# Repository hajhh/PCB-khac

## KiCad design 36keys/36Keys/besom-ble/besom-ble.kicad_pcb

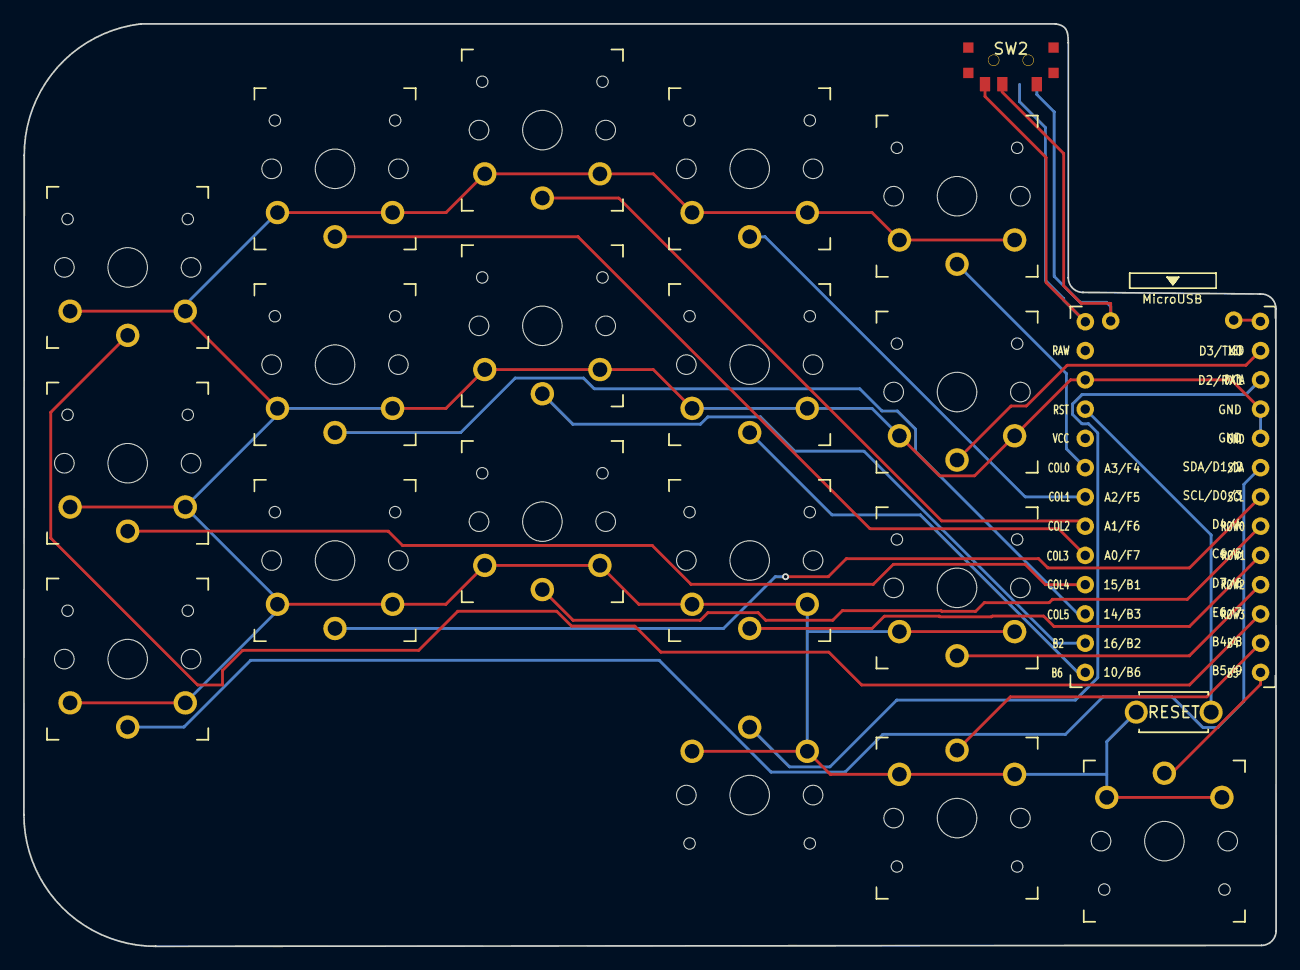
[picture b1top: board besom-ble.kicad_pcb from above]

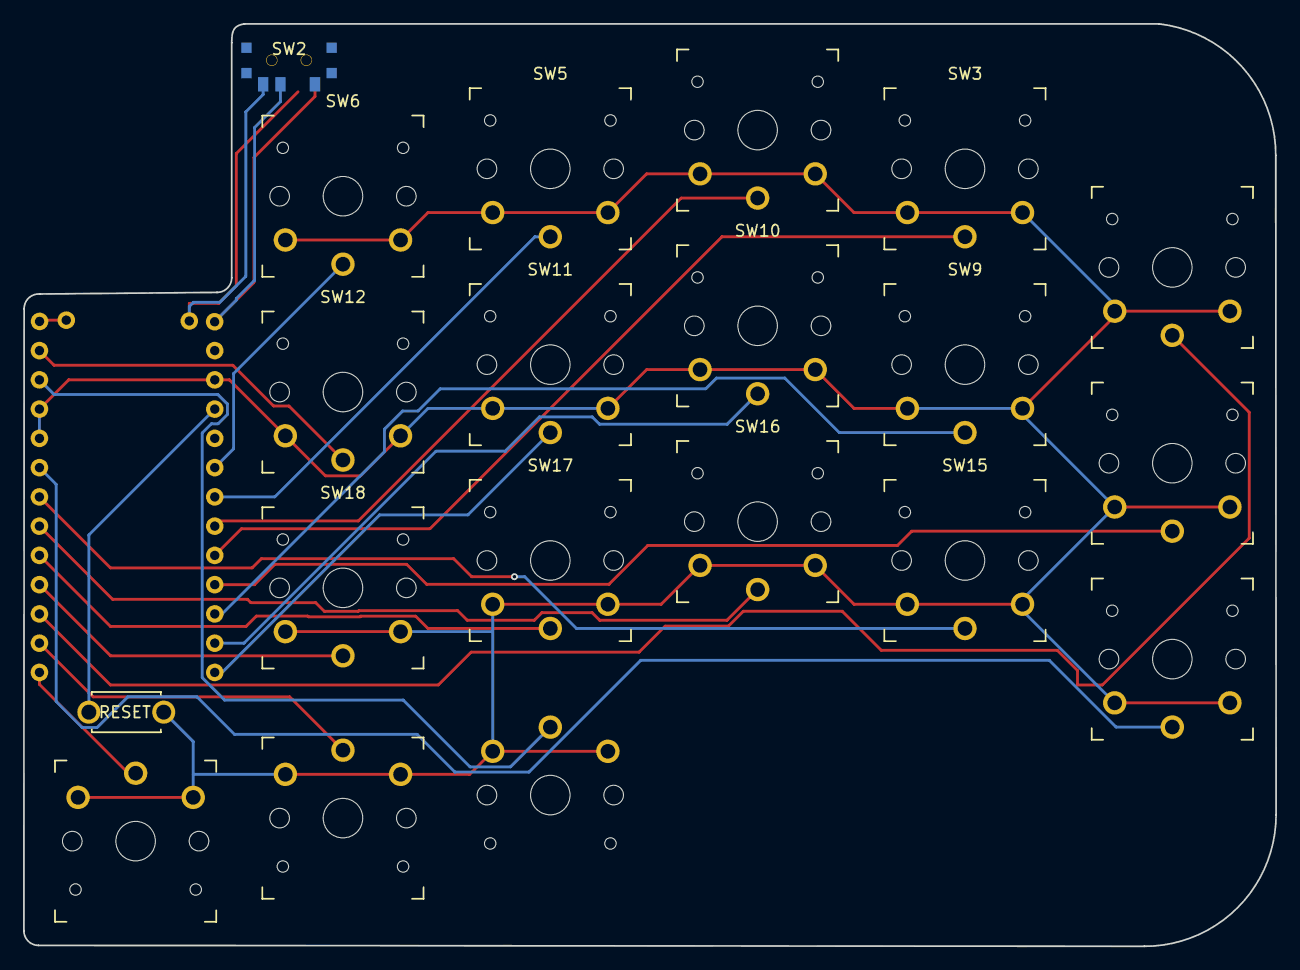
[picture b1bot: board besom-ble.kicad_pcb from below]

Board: 2 copper layers, 108.7 x 80.1 mm, 22 parts (4 on the bottom side), 20 nets.

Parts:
RSW1: Val**; ResetSW
SW2: SW_SPDT; SPDT_C128955r
SW2#2: SW_SPDT; SPDT_C128955
SW2#3, SW3, SW4, SW5, SW6, SW8, SW9, SW10, SW11, SW12, SW14, SW15, SW16, SW17, SW18, SW20, SW21, SW22: SW_PUSH; SW_PG1350_reversible_b2
U1: ProMicro; ProMicro_v3_nn

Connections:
GND: RSW1.2, SW2#3.2, SW3.2, SW4.2, SW5.2, SW6.2, SW8.2, SW9.2, SW10.2, SW11.2, SW12.2, SW14.2, SW15.2, SW16.2, SW17.2, SW18.2, SW20.2, SW21.2, SW22.2, U1.3, U1.4, U1.23
LED: SW12.1, U1.1
unnamed: SW6.1, U1.20
unnamed: SW20.1, U1.11
unnamed: SW21.1, U1.12
unnamed: SW11.1, U1.13
unnamed: SW10.1, U1.14
SCL: SW15.1, U1.6
SDA: SW14.1, U1.5
col1: SW5.1, U1.19
col2: SW4.1, U1.18
col3: SW3.1, U1.17
col4: SW8.1, U1.16
col5: SW9.1, U1.15
data: SW22.1, U1.2
reset: RSW1.1, U1.22
row0: SW16.1, U1.7
row1: SW17.1, U1.8
row2: SW18.1, U1.9
row3: SW2#3.1, U1.10

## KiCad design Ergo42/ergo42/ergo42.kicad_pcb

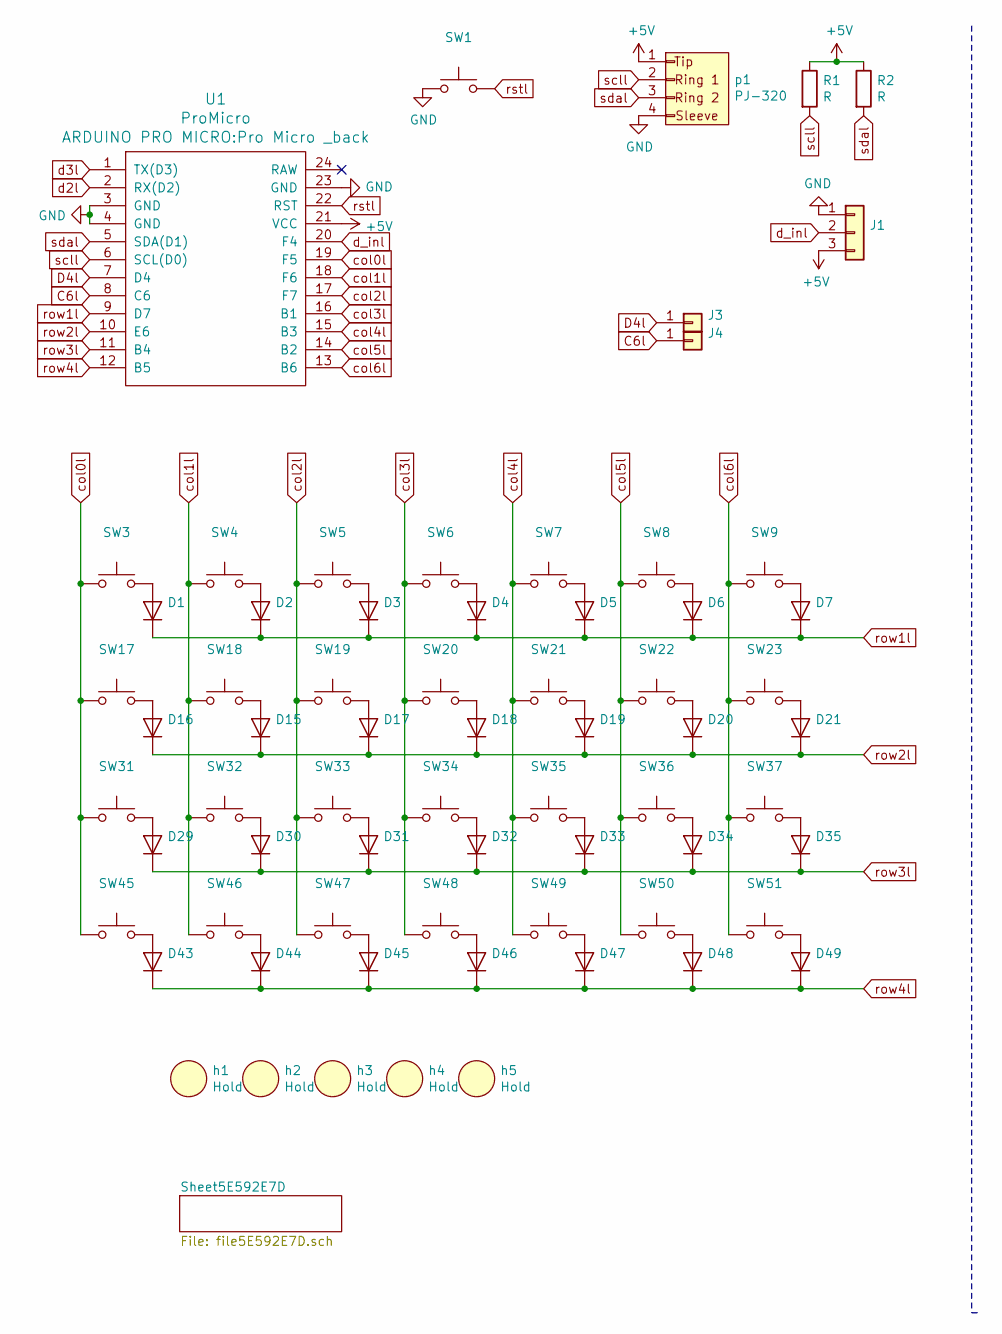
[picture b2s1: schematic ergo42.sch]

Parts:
D1, D2, D3, D4, D5, D6, D7, D15, D16, D17, D18, D19, D20, D21, D29, D30, D31, D32, D33, D34, D35, D43, D44, D45, D46, D47, D48, D49: Diode_2
J1: PinHeader_1x03_P2.54mm_Vertical
J3, J4: testpoind
R1, R2: R; R_1
SW1: RST
SW3, SW4, SW5, SW6, SW7, SW8, SW9, SW17, SW18, SW19, SW20, SW21, SW22, SW23, SW31, SW32, SW33, SW34, SW35, SW36, SW37, SW45, SW46, SW47, SW48, SW49, SW50, SW51: 1u
U1: ProMicro; Pro Micro _back
h1, h2, h3, h4, h5: Hold; Hole
p1: PJ-320; PJ-320A

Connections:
+5V: J1.3, R1.1, R2.1, U1.21 (VCC), p1.1
C6l: J4.1, U1.8 (C6)
D4l: J3.1, U1.7 (D4)
GND: J1.1, SW1.1, U1.3 (GND), U1.4 (GND), U1.23 (GND), p1.4
unnamed: D1.2 (A), SW3.2
unnamed: D2.2 (A), SW4.2
unnamed: D3.2 (A), SW5.1
unnamed: D4.2 (A), SW6.1
unnamed: D5.2 (A), SW7.1
unnamed: D6.2 (A), SW8.1
unnamed: D7.2 (A), SW9.1
unnamed: D15.2 (A), SW18.2
unnamed: D16.2 (A), SW17.2
unnamed: D17.2 (A), SW19.1
unnamed: D18.2 (A), SW20.1
unnamed: D19.2 (A), SW21.1
unnamed: D20.2 (A), SW22.1
unnamed: D21.2 (A), SW23.1
unnamed: D29.2 (A), SW31.2
unnamed: D30.2 (A), SW32.2
unnamed: D31.2 (A), SW33.1
unnamed: D32.2 (A), SW34.1
unnamed: D33.2 (A), SW35.1
unnamed: D34.2 (A), SW36.1
unnamed: D35.2 (A), SW37.1
unnamed: D43.2 (A), SW45.2
unnamed: D44.2 (A), SW46.2
unnamed: D45.2 (A), SW47.1
unnamed: D46.2 (A), SW48.1
unnamed: D47.2 (A), SW49.1
unnamed: D48.2 (A), SW50.1
unnamed: D49.2 (A), SW51.1
col0l: SW3.1, SW17.1, SW31.1, SW45.1, U1.19 (F5)
col1l: SW4.1, SW18.1, SW32.1, SW46.1, U1.18 (F6)
col2l: SW5.2, SW19.2, SW33.2, SW47.2, U1.17 (F7)
col3l: SW6.2, SW20.2, SW34.2, SW48.2, U1.16 (B1)
col4l: SW7.2, SW21.2, SW35.2, SW49.2, U1.15 (B3)
col5l: SW8.2, SW22.2, SW36.2, SW50.2, U1.14 (B2)
col6l: SW9.2, SW23.2, SW37.2, SW51.2, U1.13 (B6)
d2l: U1.2 (RX(D2))
d3l: U1.1 (TX(D3))
d_inl: J1.2, U1.20 (F4)
row1l: D1.1 (K), D2.1 (K), D3.1 (K), D4.1 (K), D5.1 (K), D6.1 (K), D7.1 (K), U1.9 (D7)
row2l: D15.1 (K), D16.1 (K), D17.1 (K), D18.1 (K), D19.1 (K), D20.1 (K), D21.1 (K), U1.10 (E6)
row3l: D29.1 (K), D30.1 (K), D31.1 (K), D32.1 (K), D33.1 (K), D34.1 (K), D35.1 (K), U1.11 (B4)
row4l: D43.1 (K), D44.1 (K), D45.1 (K), D46.1 (K), D47.1 (K), D48.1 (K), D49.1 (K), U1.12 (B5)
rstl: SW1.2, U1.22 (RST)
scll: R1.2, U1.6 (SCL(D0)), p1.2
sdal: R2.2, U1.5 (SDA(D1)), p1.3

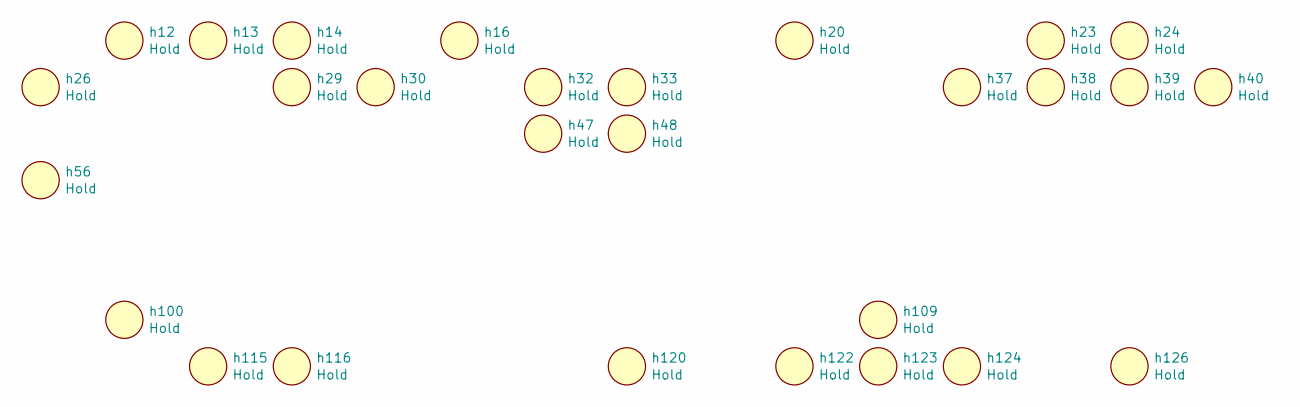
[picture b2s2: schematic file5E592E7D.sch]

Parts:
h12, h13, h14, h16, h20, h23, h24, h26, h29, h30, h32, h33, h37, h38, h39, h40, h47, h48, h56, h100, h109, h115, h116, h120, h122, h123, h124, h126: Hold; Led hole

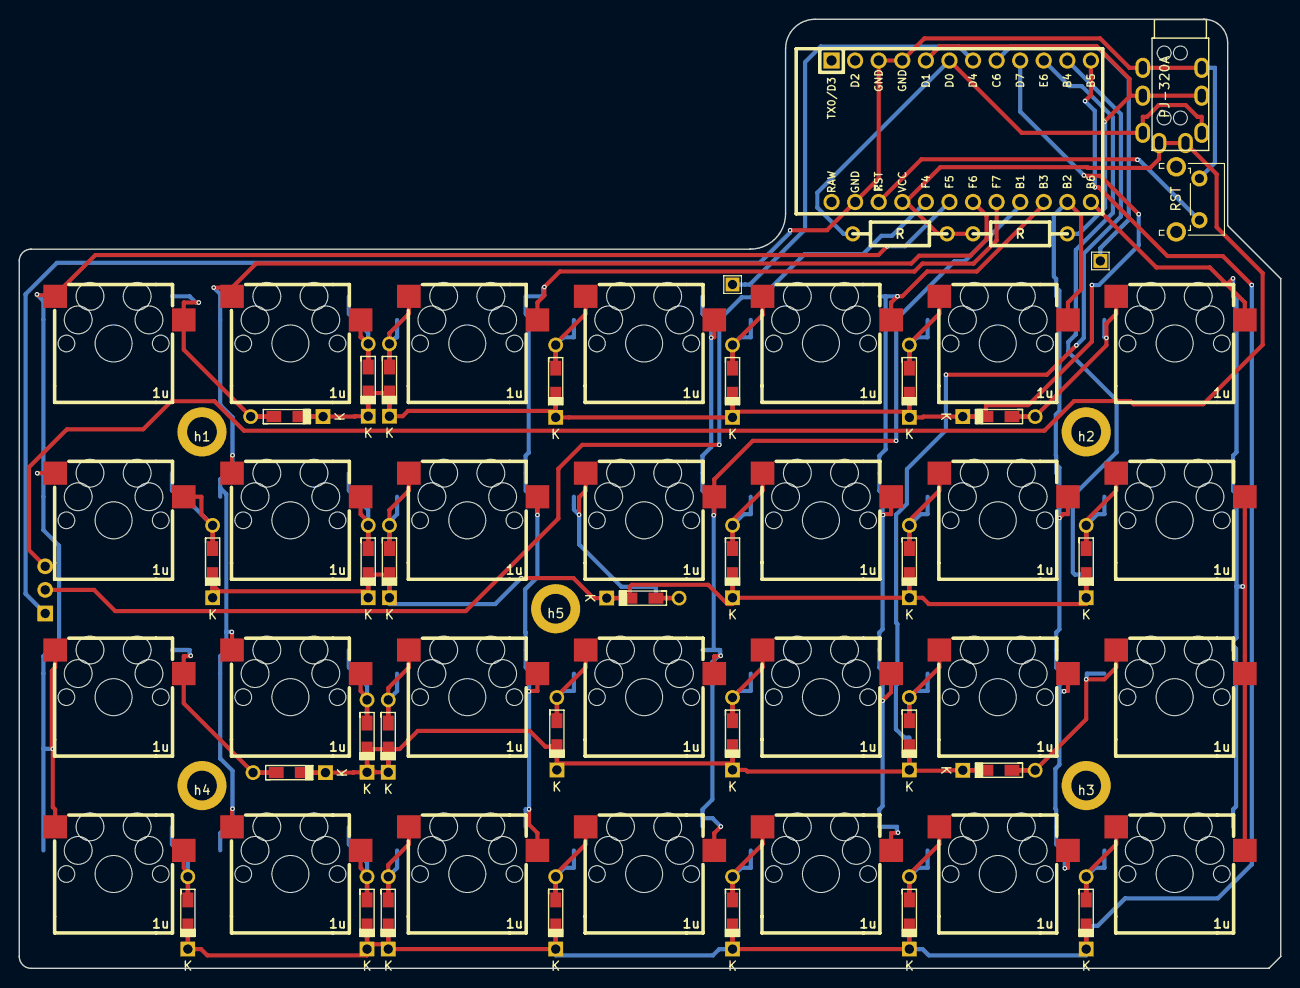
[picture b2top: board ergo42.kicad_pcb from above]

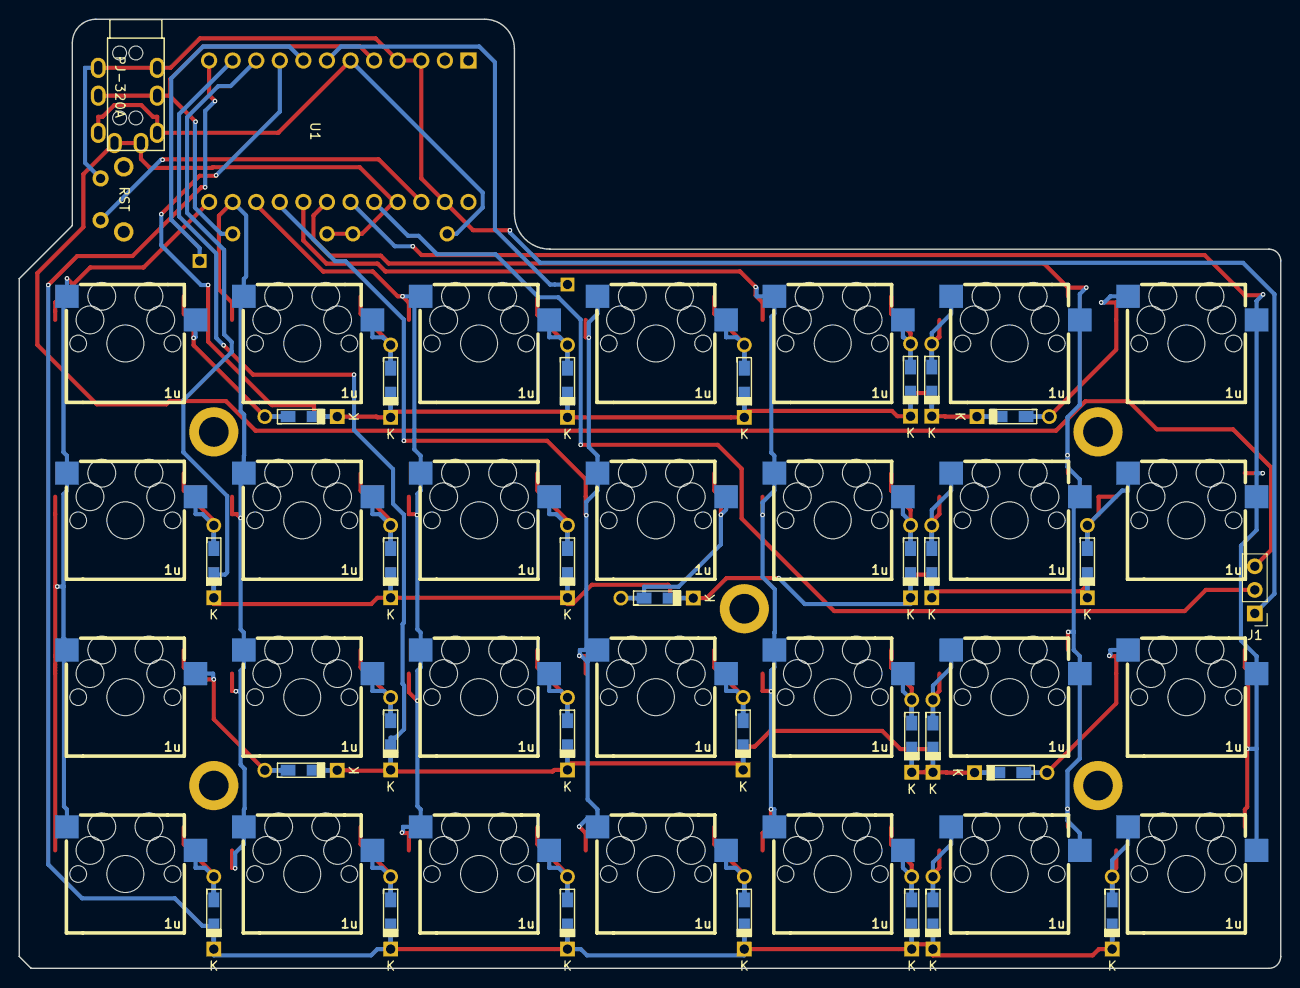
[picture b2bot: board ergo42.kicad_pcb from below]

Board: 2 copper layers, 135.9 x 102.2 mm, 97 parts (2 on the bottom side), 47 nets.

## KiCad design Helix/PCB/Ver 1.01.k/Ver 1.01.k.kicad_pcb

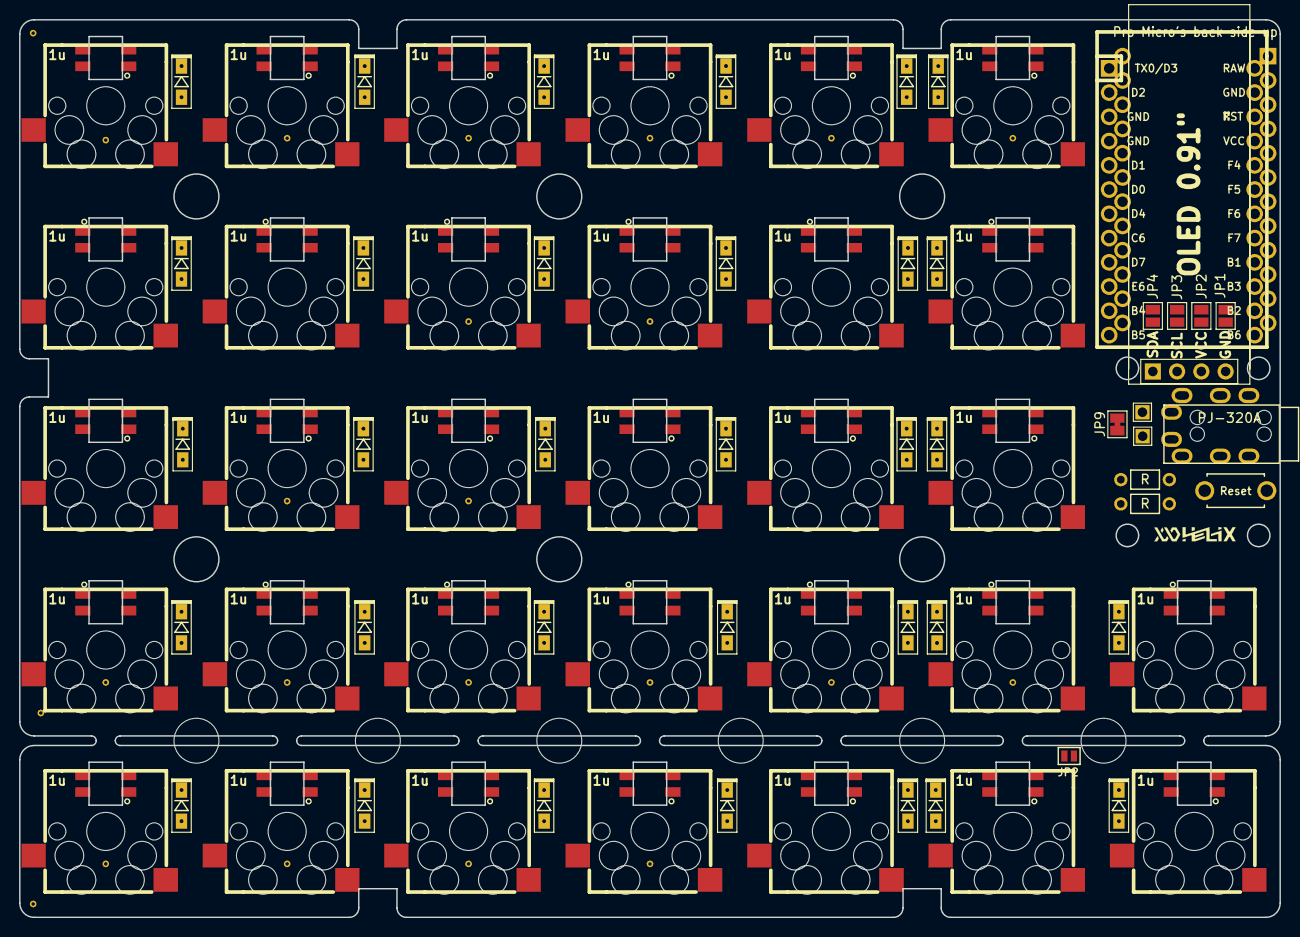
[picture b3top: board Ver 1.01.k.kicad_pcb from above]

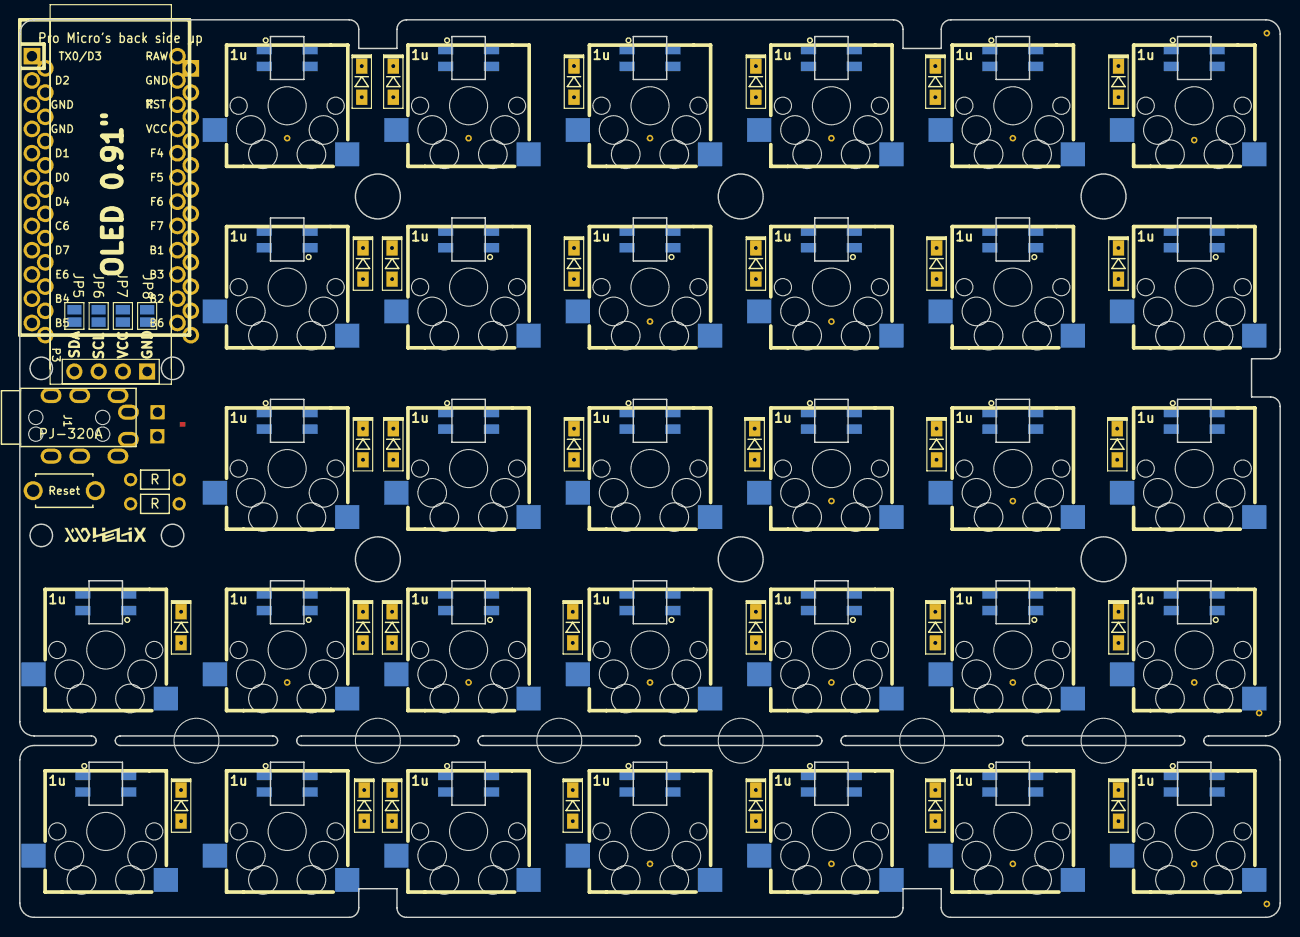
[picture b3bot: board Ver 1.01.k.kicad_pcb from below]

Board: 2 copper layers, 132.0 x 94.0 mm, 120 parts (4 on the bottom side), 85 nets, no tracks yet.

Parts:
D1, D2, D3, D4, D5, D6, D7, D8, D9, D10, D11, D12, D13, D14, D15, D16, D17, D18, D19, D20, D21, D22, D23, D24, D25, D26, D27, D28, D29, D30, D31, D32: 1N4148_smd
HOLE_3M, HOLE_3M#2, HOLE_3M#3, HOLE_3M#4, HOLE_3M#5, HOLE_3M#6: VAL**; HOLE_M2_TH
J1, J2: testpoind
JP1, JP2, JP3, JP4, JP5, JP6, JP7, JP8: SolderJumper-2_P1.3mm_Open_Pad1.0x1.5mm
JP2#2: JP2; Jumper
JP9: SolderJumper-2_P1.3mm_Bridged_Pad1.0x1.5mm
O1: OLED
R1, R2: R
SW1, SW2, SW3, SW4, SW5, SW6, SW7, SW8, SW9, SW10, SW11, SW12, SW13, SW14, SW15, SW16, SW17, SW18, SW19, SW20, SW21, SW22, SW23, SW24, SW25, SW26, SW27, SW28, SW29, SW30, SW31, SW32: 1u
SW33: Reset; SW_3.5x6.0_TH
U1: ProMicro; ProMicro_V2
U2, U3, U4, U5, U6, U7, U8, U9, U10, U11, U12, U13, U14, U15, U16, U17, U18, U19, U20, U21, U22, U23, U24, U25, U26, U27, U28, U29, U30, U31, U32, U33: SK6812mini; SK6812MINI_rev
p1: PJ-320; PJ-320A

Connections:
GND: JP1.2, JP8.2, SW33.1, U1.3, U1.4, U1.23, U2.2, U3.2, U4.2, U5.2, U6.2, U7.2, U8.2, U9.2, U10.2, U11.2, U12.2, U13.2, U14.2, U15.2, U16.2, U17.2, U18.2, U19.2, U20.2, U21.2, U22.2, U23.2, U24.2, U25.2, U26.2, U27.2, U28.2, U29.2, U30.2, U31.2, U32.2, U33.2, p1.3
LED: U1.1, U7.3
unnamed: D1.2, SW1.2
unnamed: D2.2, SW2.2
unnamed: D3.2, SW3.2
unnamed: D4.2, SW4.2
unnamed: D5.2, SW5.2
unnamed: D6.2, SW6.1
unnamed: D7.2, SW7.2
unnamed: D8.2, SW8.2
unnamed: D9.2, SW9.2
unnamed: D10.2, SW10.2
unnamed: D11.2, SW11.2
unnamed: D12.2, SW12.1
unnamed: D13.2, SW13.2
unnamed: D14.2, SW14.2
unnamed: D15.2, SW15.2
unnamed: D16.2, SW16.2
unnamed: D17.2, SW17.2
unnamed: D18.2, SW18.1
unnamed: D19.2, SW19.2
unnamed: D20.2, SW20.2
unnamed: D21.2, SW21.2
unnamed: D22.2, SW22.2
unnamed: D23.2, SW23.2
unnamed: D24.2, SW24.1
unnamed: D25.2, SW25.1
unnamed: D26.2, SW26.2
unnamed: D27.2, SW27.2
unnamed: D28.2, SW28.2
unnamed: D29.2, SW29.2
unnamed: D30.2, SW30.2
unnamed: D31.2, SW31.1
unnamed: D32.2, SW32.1
unnamed: J1.1, p1.1
unnamed: J2.1, JP9.1, p1.4
unnamed: JP1.1, JP5.1, O1.1
unnamed: JP2.1, JP2#2.1, JP6.1, O1.2, U32.3, U33.1
unnamed: JP2#2.2, U25.1, U26.3
unnamed: JP3.1, JP7.1, O1.3, U26.1, U33.3
unnamed: JP4.1, JP8.1, O1.4
unnamed: U2.1, U8.3
unnamed: U2.3, U3.1
unnamed: U3.3, U4.1
unnamed: U4.3, U5.1
unnamed: U5.3, U6.1
unnamed: U6.3, U7.1
unnamed: U8.1, U9.3
unnamed: U10.1, U11.3
unnamed: U9.1, U10.3
unnamed: U11.1, U12.3
unnamed: U12.1, U13.3
unnamed: U13.1, U19.3
unnamed: U14.1, U20.3
unnamed: U14.3, U15.1
unnamed: U15.3, U16.1
unnamed: U16.3, U17.1
unnamed: U17.3, U18.1
unnamed: U18.3, U19.1
unnamed: U20.1, U21.3
unnamed: U21.1, U22.3
unnamed: U22.1, U23.3
unnamed: U23.1, U24.3
unnamed: U24.1, U25.3
unnamed: U27.3, U28.1
unnamed: U28.3, U29.1
unnamed: U29.3, U30.1
unnamed: U30.3, U31.1
unnamed: U31.3, U32.1
VCC: JP2.2, JP7.2, R1.2, R2.2, U1.21, U1.24, U2.4, U3.4, U4.4, U5.4, U6.4, U7.4, U8.4, U9.4, U10.4, U11.4, U12.4, U13.4, U14.4, U15.4, U16.4, U17.4, U18.4, U19.4, U20.4, U21.4, U22.4, U23.4, U24.4, U25.4, U26.4, U27.4, U28.4, U29.4, U30.4, U31.4, U32.4, U33.4, p1.2
col0: SW1.1, SW7.1, SW13.1, SW19.1, SW26.1, U1.20
col1: SW2.1, SW8.1, SW14.1, SW20.1, SW27.1, U1.19
col2: SW3.1, SW9.1, SW15.1, SW21.1, SW28.1, U1.18
col3: SW4.1, SW10.1, SW16.1, SW22.1, SW29.1, U1.17
col4: SW5.1, SW11.1, SW17.1, SW23.1, SW30.1, U1.16
col5: SW6.2, SW12.2, SW18.2, SW24.2, SW31.2, U1.15
col6: SW25.2, SW32.2, U1.14
data: JP9.2, U1.2
row0: D1.1, D2.1, D3.1, D4.1, D5.1, D6.1, U1.7
row1: D7.1, D8.1, D9.1, D10.1, D11.1, D12.1, U1.8
row2: D13.1, D14.1, D15.1, D16.1, D17.1, D18.1, U1.9
row3: D19.1, D20.1, D21.1, D22.1, D23.1, D24.1, D25.1, U1.10
row4: D26.1, D27.1, D28.1, D29.1, D30.1, D31.1, D32.1, U1.11
scl: JP3.2, JP6.2, R2.1, U1.6
sda: JP4.2, JP5.2, R1.1, U1.5

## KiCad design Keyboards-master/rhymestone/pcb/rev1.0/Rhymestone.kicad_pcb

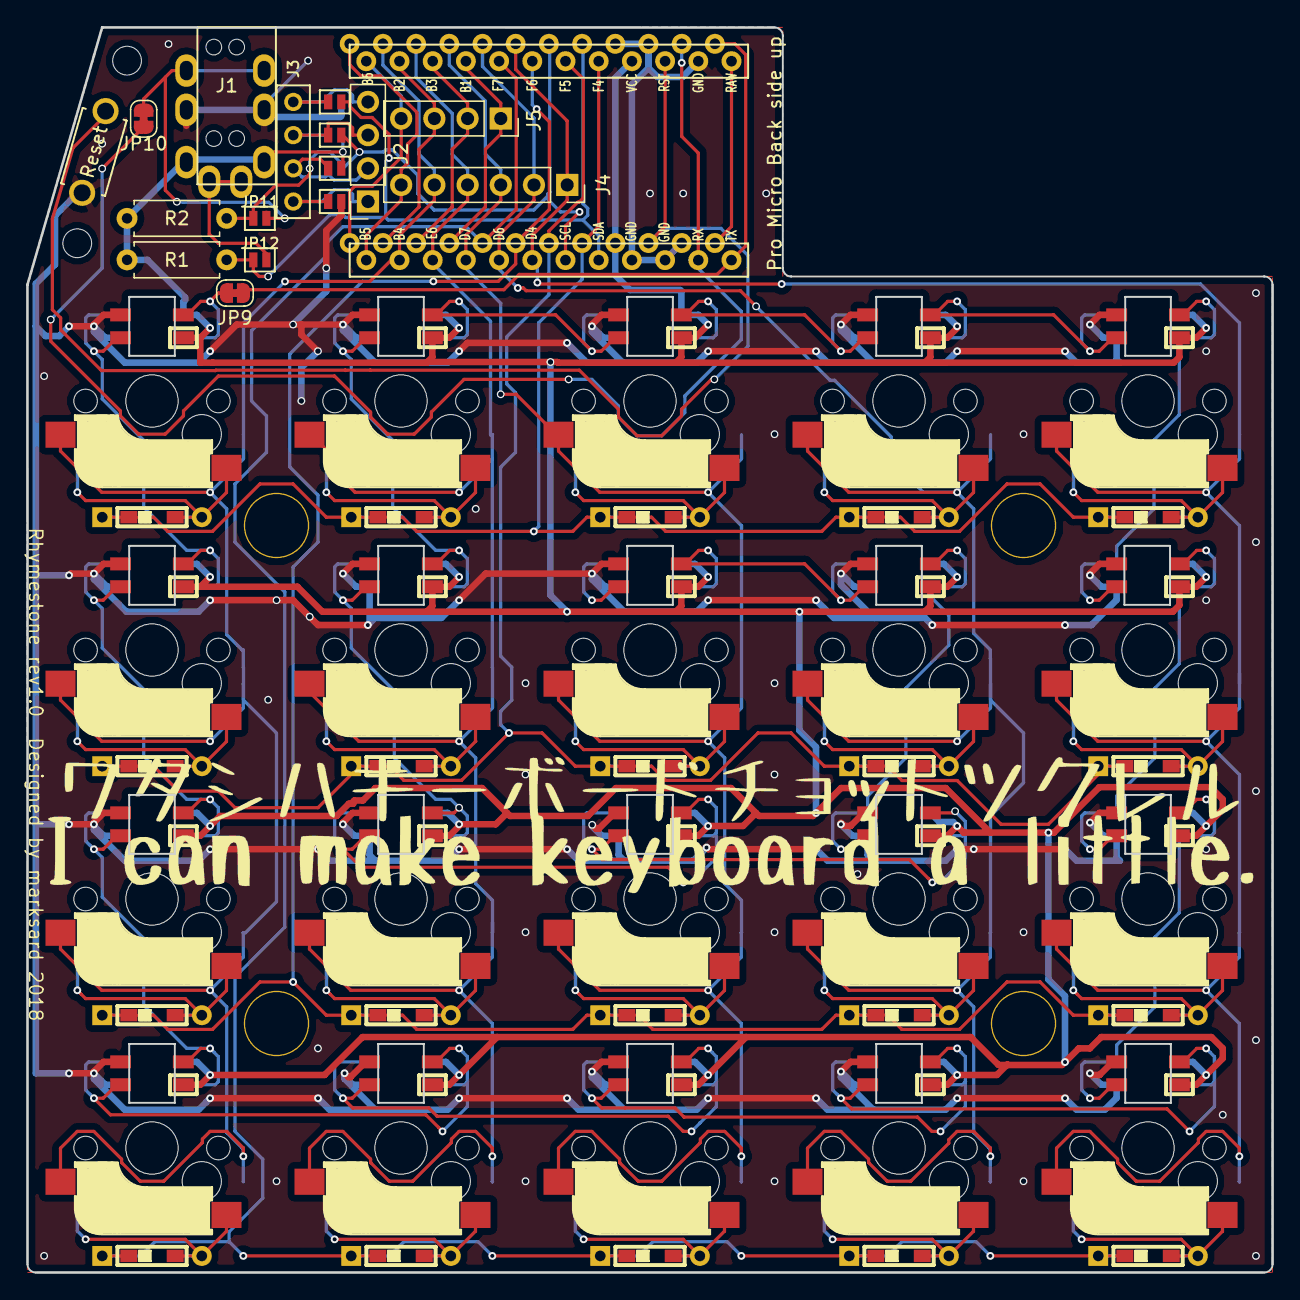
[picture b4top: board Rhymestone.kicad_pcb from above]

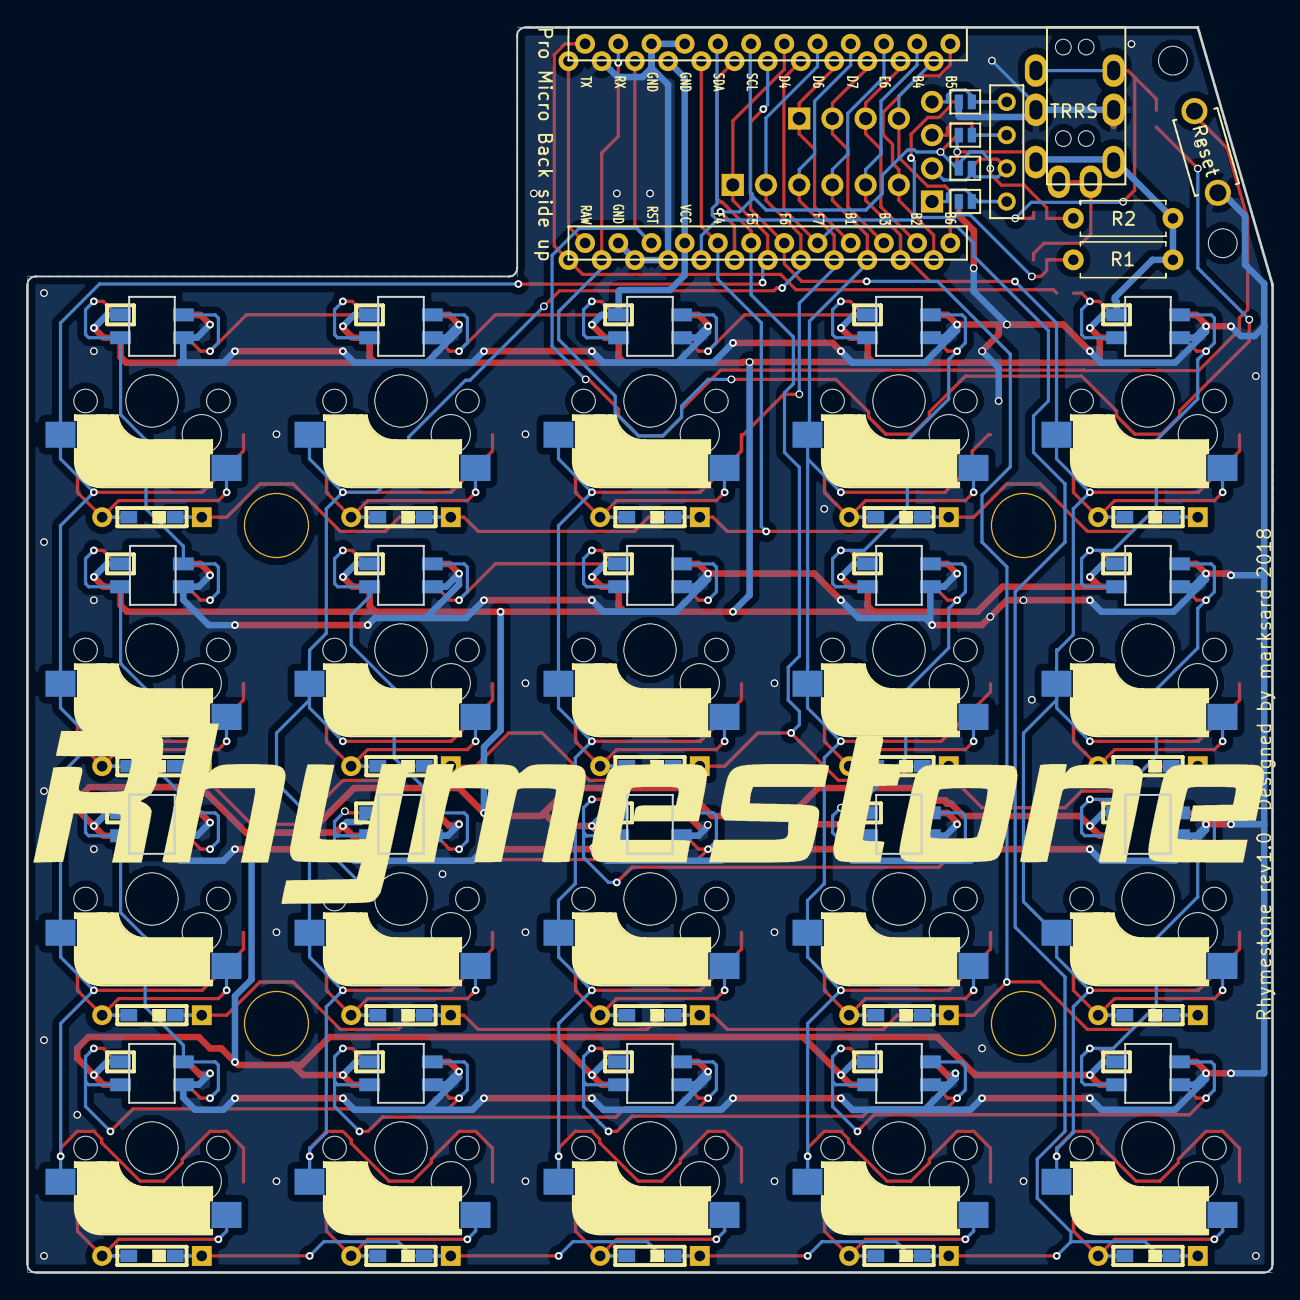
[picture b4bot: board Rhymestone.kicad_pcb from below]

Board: 2 copper layers, 95.3 x 95.3 mm, 87 parts (4 on the bottom side), 67 nets.

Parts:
D1, D2, D3, D4, D5, D6, D7, D8, D9, D10, D11, D12, D13, D14, D15, D16, D17, D18, D19, D20: D; D3_SMD
J1: MJ-4PP-9
J2: AUX; PinSocket_1x04_P2.54mm_Vertical
J3: OLED
J4: Columns; PinSocket_1x06_P2.54mm_Vertical
J5: Rows; PinSocket_1x04_P2.54mm_Vertical
JP1, JP2, JP3, JP4, JP5, JP6, JP7, JP8: Jumper
JP9: LED; SolderJumper-2_P1.3mm_Bridged_RoundedPad1.0x1.5mm
JP10: DataJP; SolderJumper-2_P1.3mm_Bridged_RoundedPad1.0x1.5mm
JP11: SDLJP; Jumper
JP12: SDAJP; Jumper
L1, L2, L3, L4, L5, L6, L7, L8, L9, L10, L11, L12, L13, L14, L15, L16, L17, L18, L19, L20: SK6812MINI; SK6812MINI_rev
R1, R2: R; R_TH
RSW1: Reset; ResetSW
SW1, SW2, SW3, SW4, SW5, SW6, SW7, SW8, SW9, SW10, SW11, SW12, SW13, SW14, SW15, SW16, SW17, SW18, SW19, SW20: SW_PUSH; CherryMX_Hotswap
U1: ProMicro; ProMicro_v2
h1, h2, h3, h4: hole; LEGO_HOLE
h7, h8: hole; LEGO_HOLE2

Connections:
GND: J1.C, JP1.1, JP8.1, L1.2, L2.2, L3.2, L4.2, L5.2, L6.2, L7.2, L8.2, L9.2, L10.2, L11.2, L12.2, L13.2, L14.2, L15.2, L16.2, L17.2, L18.2, L19.2, L20.2, RSW1.2, U1.3, U1.4, U1.23
LED: JP9.2, U1.1
unnamed: D1.2, SW1.2
unnamed: D2.2, SW2.2
unnamed: D3.2, SW3.2
unnamed: D4.2, SW4.2
unnamed: D5.2, SW5.2
unnamed: D6.2, SW6.2
unnamed: D7.2, SW7.2
unnamed: D8.2, SW8.2
unnamed: D9.2, SW9.2
unnamed: D10.2, SW10.2
unnamed: D11.2, SW11.2
unnamed: D12.2, SW12.2
unnamed: D13.2, SW13.2
unnamed: D14.2, SW14.2
unnamed: D15.2, SW15.2
unnamed: D16.2, SW16.2
unnamed: D17.2, SW17.2
unnamed: D18.2, SW18.2
unnamed: D19.2, SW19.2
unnamed: D20.2, SW20.2
unnamed: J1.A, JP12.2
unnamed: J1.B, JP10.2, JP11.2
unnamed: J2.1, J3.1, JP1.2, JP5.2
unnamed: J2.2, J3.2, JP2.2, JP6.2
unnamed: J2.3, J3.3, JP3.2, JP7.2
unnamed: J2.4, J3.4, JP4.2, JP8.2
unnamed: JP9.1, L1.3
unnamed: L1.1, L2.3
unnamed: L2.1, L3.3
unnamed: L3.1, L4.3
unnamed: L4.1, L5.3
unnamed: L5.1, L6.3
unnamed: L6.1, L7.3
unnamed: L7.1, L8.3
unnamed: L8.1, L9.3
unnamed: L10.1, L11.3
unnamed: L9.1, L10.3
unnamed: L11.1, L12.3
unnamed: L12.1, L13.3
unnamed: L13.1, L14.3
unnamed: L14.1, L15.3
unnamed: L15.1, L16.3
unnamed: L16.1, L17.3
unnamed: L17.1, L18.3
unnamed: L18.1, L19.3
unnamed: L19.1, L20.3
SCL: JP3.1, JP6.1, JP11.1, R2.1, U1.6
SDA: JP4.1, JP5.1, JP12.1, R1.2, U1.5
VCC: J1.D, JP2.1, JP7.1, L1.4, L2.4, L3.4, L4.4, L5.4, L6.4, L7.4, L8.4, L9.4, L10.4, L11.4, L12.4, L13.4, L14.4, L15.4, L16.4, L17.4, L18.4, L19.4, L20.4, R1.1, R2.2, U1.21
col0: J4.1, SW1.1, SW2.1, SW3.1, SW4.1, U1.7
col1: J4.2, SW5.1, SW6.1, SW7.1, SW8.1, U1.8
col2: J4.3, SW9.1, SW10.1, SW11.1, SW12.1, U1.9
col3: J4.4, SW13.1, SW14.1, SW15.1, SW16.1, U1.10
col4: J4.5, SW17.1, SW18.1, SW19.1, SW20.1, U1.11
col5: J4.6, U1.12
data: JP10.1, U1.2
reset: RSW1.1, U1.22
row0: D1.1, D5.1, D9.1, D13.1, D17.1, U1.20
row1: D2.1, D6.1, D10.1, D14.1, D18.1, U1.19
row2: D3.1, D7.1, D11.1, D15.1, D19.1, U1.18
row3: D4.1, D8.1, D12.1, D16.1, D20.1, U1.17
row4: J5.1, U1.16
row5: J5.2, U1.15
row6: J5.3, U1.14
row7: J5.4, U1.13
